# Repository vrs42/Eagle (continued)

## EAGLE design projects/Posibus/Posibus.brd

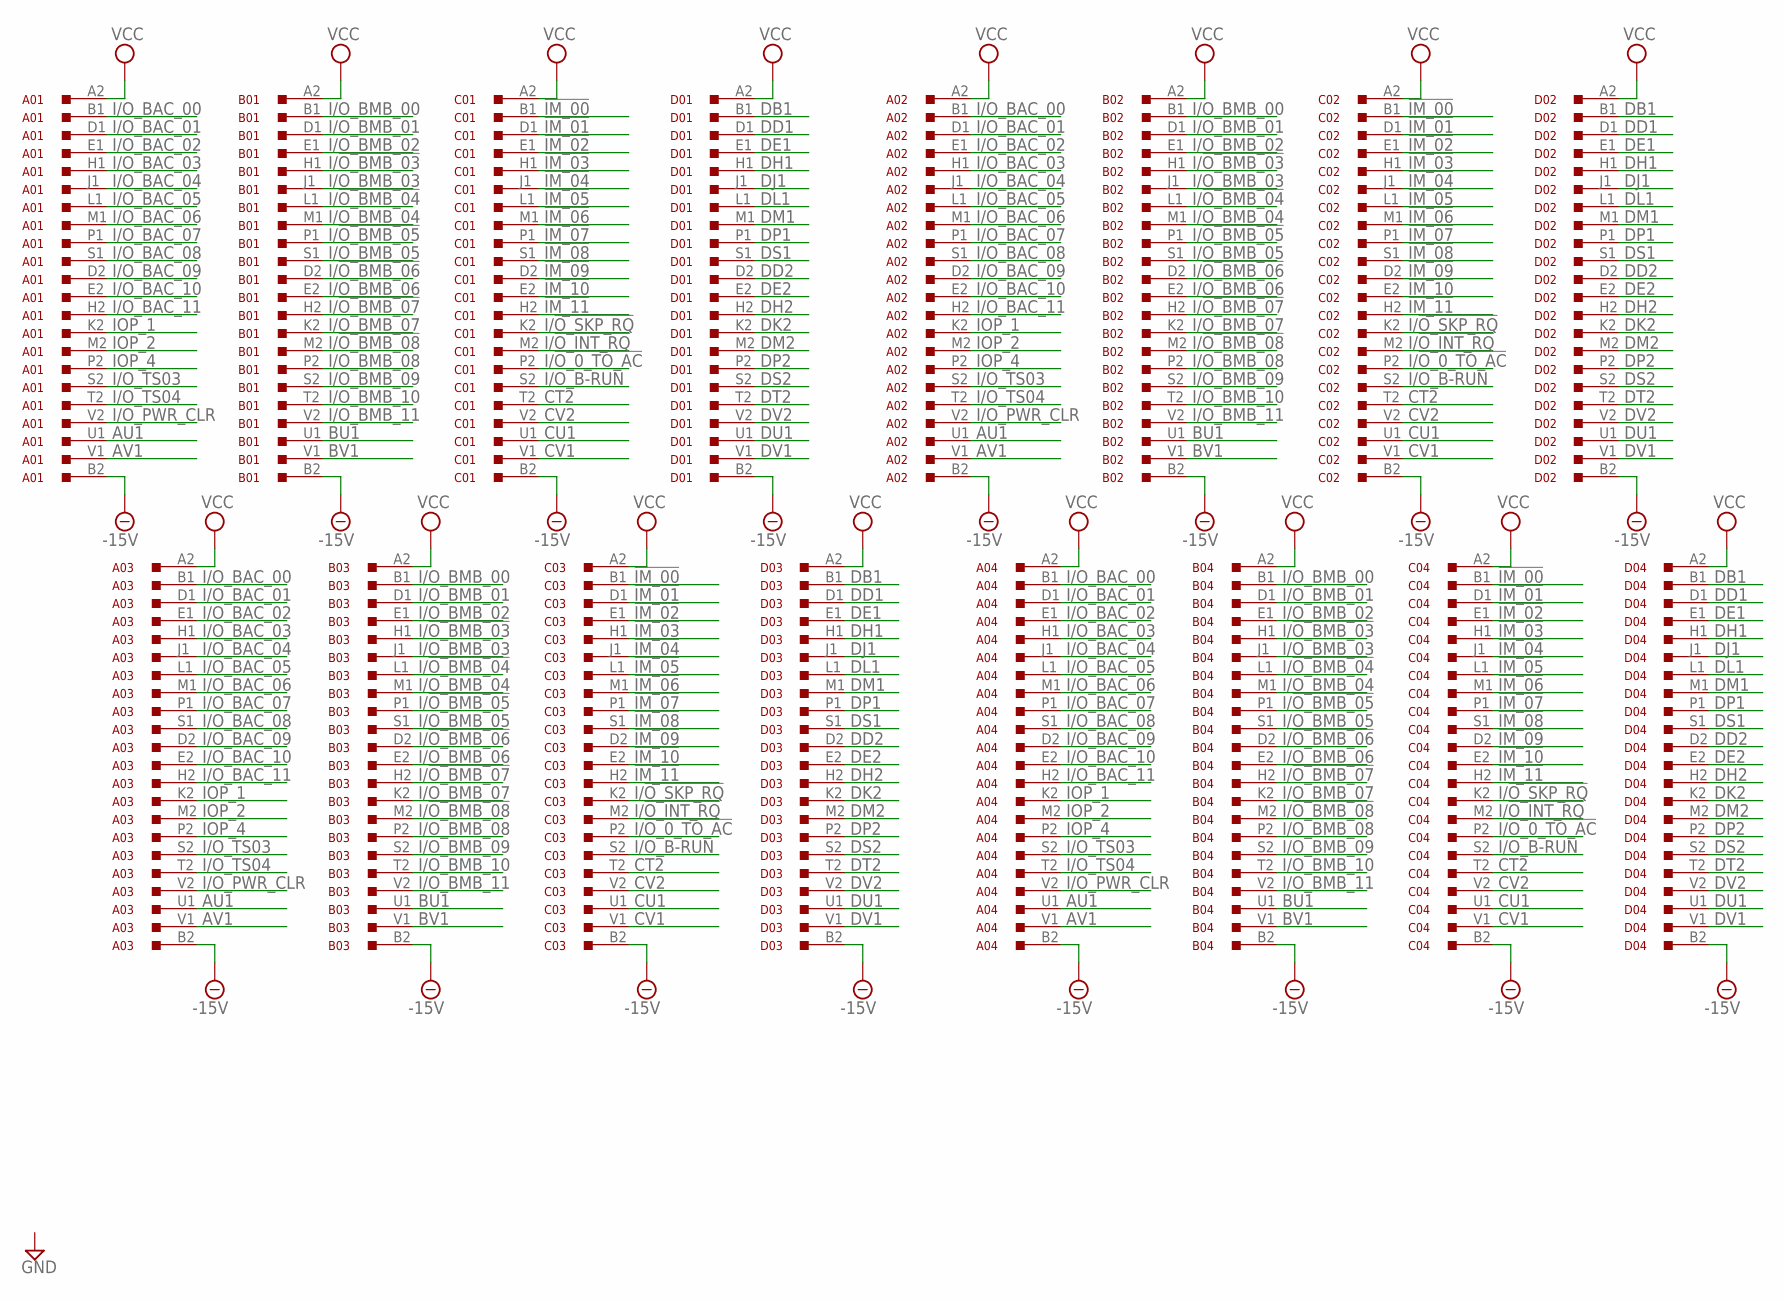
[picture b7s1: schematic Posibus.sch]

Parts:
A01, A02, A03, A04: M903; H807
B01, B02, B03, B04: M903; H807
C01, C02, C03, C04: M903; H807
D01, D02, D03, D04: M903; H807

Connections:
!IM_00: C01.B1, C02.B1, C03.B1, C04.B1
!IM_01: C01.D1, C02.D1, C03.D1, C04.D1
!IM_02: C01.E1, C02.E1, C03.E1, C04.E1
!IM_03: C01.H1, C02.H1, C03.H1, C04.H1
!IM_04: C01.J1, C02.J1, C03.J1, C04.J1
!IM_05: C01.L1, C02.L1, C03.L1, C04.L1
!IM_06: C01.M1, C02.M1, C03.M1, C04.M1
!IM_07: C01.P1, C02.P1, C03.P1, C04.P1
!IM_08: C01.S1, C02.S1, C03.S1, C04.S1
!IM_09: C01.D2, C02.D2, C03.D2, C04.D2
!IM_10: C01.E2, C02.E2, C03.E2, C04.E2
!IM_11: C01.H2, C02.H2, C03.H2, C04.H2
-15V: A01.B2, A02.B2, A03.B2, A04.B2, B01.B2, B02.B2, B03.B2, B04.B2, C01.B2, C02.B2, C03.B2, C04.B2, D01.B2, D02.B2, D03.B2, D04.B2
AU1: A01.U1, A02.U1, A03.U1, A04.U1
AV1: A01.V1, A02.V1, A03.V1, A04.V1
BU1: B01.U1, B02.U1, B03.U1, B04.U1
BV1: B01.V1, B02.V1, B03.V1, B04.V1
CT2: C01.T2, C02.T2, C03.T2, C04.T2
CU1: C01.U1, C02.U1, C03.U1, C04.U1
CV1: C01.V1, C02.V1, C03.V1, C04.V1
CV2: C01.V2, C02.V2, C03.V2, C04.V2
DB1: D01.B1, D02.B1, D03.B1, D04.B1
DD1: D01.D1, D02.D1, D03.D1, D04.D1
DD2: D01.D2, D02.D2, D03.D2, D04.D2
DE1: D01.E1, D02.E1, D03.E1, D04.E1
DE2: D01.E2, D02.E2, D03.E2, D04.E2
DH1: D01.H1, D02.H1, D03.H1, D04.H1
DH2: D01.H2, D02.H2, D03.H2, D04.H2
DJ1: D01.J1, D02.J1, D03.J1, D04.J1
DK2: D01.K2, D02.K2, D03.K2, D04.K2
DL1: D01.L1, D02.L1, D03.L1, D04.L1
DM1: D01.M1, D02.M1, D03.M1, D04.M1
DM2: D01.M2, D02.M2, D03.M2, D04.M2
DP1: D01.P1, D02.P1, D03.P1, D04.P1
DP2: D01.P2, D02.P2, D03.P2, D04.P2
DS1: D01.S1, D02.S1, D03.S1, D04.S1
DS2: D01.S2, D02.S2, D03.S2, D04.S2
DT2: D01.T2, D02.T2, D03.T2, D04.T2
DU1: D01.U1, D02.U1, D03.U1, D04.U1
DV1: D01.V1, D02.V1, D03.V1, D04.V1
DV2: D01.V2, D02.V2, D03.V2, D04.V2
GND: A01.A1 (GND), A01.C1 (GND), A01.C2 (GND), A01.F1 (GND), A01.F2 (GND), A01.J2 (GND), A01.K1 (GND), A01.L2 (GND), A01.N1 (GND), A01.N2 (GND), A01.R1 (GND), A01.R2 (GND), A01.T1 (GND), A01.U2 (GND), A02.A1 (GND), A02.C1 (GND), A02.C2 (GND), A02.F1 (GND), A02.F2 (GND), A02.J2 (GND), A02.K1 (GND), A02.L2 (GND), A02.N1 (GND), A02.N2 (GND), A02.R1 (GND), A02.R2 (GND), A02.T1 (GND), A02.U2 (GND), A03.A1 (GND), A03.C1 (GND), A03.C2 (GND), A03.F1 (GND), A03.F2 (GND), A03.J2 (GND), A03.K1 (GND), A03.L2 (GND), A03.N1 (GND), A03.N2 (GND), A03.R1 (GND), A03.R2 (GND), A03.T1 (GND), A03.U2 (GND), A04.A1 (GND), A04.C1 (GND), A04.C2 (GND), A04.F1 (GND), A04.F2 (GND), A04.J2 (GND), A04.K1 (GND), A04.L2 (GND), A04.N1 (GND), A04.N2 (GND), A04.R1 (GND), A04.R2 (GND), A04.T1 (GND), A04.U2 (GND), B01.A1 (GND), B01.C1 (GND), B01.C2 (GND), B01.F1 (GND), B01.F2 (GND), B01.J2 (GND), B01.K1 (GND), B01.L2 (GND), B01.N1 (GND), B01.N2 (GND), B01.R1 (GND), B01.R2 (GND), B01.T1 (GND), B01.U2 (GND), B02.A1 (GND), B02.C1 (GND), B02.C2 (GND), B02.F1 (GND), B02.F2 (GND), B02.J2 (GND), B02.K1 (GND), B02.L2 (GND), B02.N1 (GND), B02.N2 (GND), B02.R1 (GND), B02.R2 (GND), B02.T1 (GND), B02.U2 (GND), B03.A1 (GND), B03.C1 (GND), B03.C2 (GND), B03.F1 (GND), B03.F2 (GND), B03.J2 (GND), B03.K1 (GND), B03.L2 (GND), B03.N1 (GND), B03.N2 (GND), B03.R1 (GND), B03.R2 (GND), B03.T1 (GND), B03.U2 (GND), B04.A1 (GND), B04.C1 (GND), B04.C2 (GND), B04.F1 (GND), B04.F2 (GND), B04.J2 (GND), B04.K1 (GND), B04.L2 (GND), B04.N1 (GND), B04.N2 (GND), B04.R1 (GND), B04.R2 (GND), B04.T1 (GND), B04.U2 (GND), C01.A1 (GND), C01.C1 (GND), C01.C2 (GND), C01.F1 (GND), C01.F2 (GND), C01.J2 (GND), C01.K1 (GND), C01.L2 (GND), C01.N1 (GND), C01.N2 (GND), C01.R1 (GND), C01.R2 (GND), C01.T1 (GND), C01.U2 (GND), C02.A1 (GND), C02.C1 (GND), C02.C2 (GND), C02.F1 (GND), C02.F2 (GND), C02.J2 (GND), C02.K1 (GND), C02.L2 (GND), C02.N1 (GND), C02.N2 (GND), C02.R1 (GND), C02.R2 (GND), C02.T1 (GND), C02.U2 (GND), C03.A1 (GND), C03.C1 (GND), C03.C2 (GND), C03.F1 (GND), C03.F2 (GND), C03.J2 (GND), C03.K1 (GND), C03.L2 (GND), C03.N1 (GND), C03.N2 (GND), C03.R1 (GND), C03.R2 (GND), C03.T1 (GND), C03.U2 (GND), C04.A1 (GND), C04.C1 (GND), C04.C2 (GND), C04.F1 (GND), C04.F2 (GND), C04.J2 (GND), C04.K1 (GND), C04.L2 (GND), C04.N1 (GND), C04.N2 (GND), C04.R1 (GND), C04.R2 (GND), C04.T1 (GND), C04.U2 (GND), D01.A1 (GND), D01.C1 (GND), D01.C2 (GND), D01.F1 (GND), D01.F2 (GND), D01.J2 (GND), D01.K1 (GND), D01.L2 (GND), D01.N1 (GND), D01.N2 (GND), D01.R1 (GND), D01.R2 (GND), D01.T1 (GND), D01.U2 (GND), D02.A1 (GND), D02.C1 (GND), D02.C2 (GND), D02.F1 (GND), D02.F2 (GND), D02.J2 (GND), D02.K1 (GND), D02.L2 (GND), D02.N1 (GND), D02.N2 (GND), D02.R1 (GND), D02.R2 (GND), D02.T1 (GND), D02.U2 (GND), D03.A1 (GND), D03.C1 (GND), D03.C2 (GND), D03.F1 (GND), D03.F2 (GND), D03.J2 (GND), D03.K1 (GND), D03.L2 (GND), D03.N1 (GND), D03.N2 (GND), D03.R1 (GND), D03.R2 (GND), D03.T1 (GND), D03.U2 (GND), D04.A1 (GND), D04.C1 (GND), D04.C2 (GND), D04.F1 (GND), D04.F2 (GND), D04.J2 (GND), D04.K1 (GND), D04.L2 (GND), D04.N1 (GND), D04.N2 (GND), D04.R1 (GND), D04.R2 (GND), D04.T1 (GND), D04.U2 (GND)
I/!O_0_TO_AC: C01.P2, C02.P2, C03.P2, C04.P2
I/!O_BMB_03: B01.H1, B02.H1, B03.H1, B04.H1
I/!O_BMB_04: B01.L1, B02.L1, B03.L1, B04.L1
I/!O_BMB_05: B01.P1, B02.P1, B03.P1, B04.P1
I/!O_BMB_06: B01.D2, B02.D2, B03.D2, B04.D2
I/!O_BMB_07: B01.H2, B02.H2, B03.H2, B04.H2
I/!O_BMB_08: B01.M2, B02.M2, B03.M2, B04.M2
I/!O_INT_RQ: C01.M2, C02.M2, C03.M2, C04.M2
I/!O_SKP_RQ: C01.K2, C02.K2, C03.K2, C04.K2
I/O_B-RUN: C01.S2, C02.S2, C03.S2, C04.S2
I/O_BAC_00: A01.B1, A02.B1, A03.B1, A04.B1
I/O_BAC_01: A01.D1, A02.D1, A03.D1, A04.D1
I/O_BAC_02: A01.E1, A02.E1, A03.E1, A04.E1
I/O_BAC_03: A01.H1, A02.H1, A03.H1, A04.H1
I/O_BAC_04: A01.J1, A02.J1, A03.J1, A04.J1
I/O_BAC_05: A01.L1, A02.L1, A03.L1, A04.L1
I/O_BAC_06: A01.M1, A02.M1, A03.M1, A04.M1
I/O_BAC_07: A01.P1, A02.P1, A03.P1, A04.P1
I/O_BAC_08: A01.S1, A02.S1, A03.S1, A04.S1
I/O_BAC_09: A01.D2, A02.D2, A03.D2, A04.D2
I/O_BAC_10: A01.E2, A02.E2, A03.E2, A04.E2
I/O_BAC_11: A01.H2, A02.H2, A03.H2, A04.H2
I/O_BMB_00: B01.B1, B02.B1, B03.B1, B04.B1
I/O_BMB_01: B01.D1, B02.D1, B03.D1, B04.D1
I/O_BMB_02: B01.E1, B02.E1, B03.E1, B04.E1
I/O_BMB_03: B01.J1, B02.J1, B03.J1, B04.J1
I/O_BMB_04: B01.M1, B02.M1, B03.M1, B04.M1
I/O_BMB_05: B01.S1, B02.S1, B03.S1, B04.S1
I/O_BMB_06: B01.E2, B02.E2, B03.E2, B04.E2
I/O_BMB_07: B01.K2, B02.K2, B03.K2, B04.K2
I/O_BMB_08: B01.P2, B02.P2, B03.P2, B04.P2
I/O_BMB_09: B01.S2, B02.S2, B03.S2, B04.S2
I/O_BMB_10: B01.T2, B02.T2, B03.T2, B04.T2
I/O_BMB_11: B01.V2, B02.V2, B03.V2, B04.V2
I/O_PWR_CLR: A01.V2, A02.V2, A03.V2, A04.V2
I/O_TS03: A01.S2, A02.S2, A03.S2, A04.S2
I/O_TS04: A01.T2, A02.T2, A03.T2, A04.T2
IOP_1: A01.K2, A02.K2, A03.K2, A04.K2
IOP_2: A01.M2, A02.M2, A03.M2, A04.M2
IOP_4: A01.P2, A02.P2, A03.P2, A04.P2
VCC: A01.A2, A02.A2, A03.A2, A04.A2, B01.A2, B02.A2, B03.A2, B04.A2, C01.A2, C02.A2, C03.A2, C04.A2, D01.A2, D02.A2, D03.A2, D04.A2

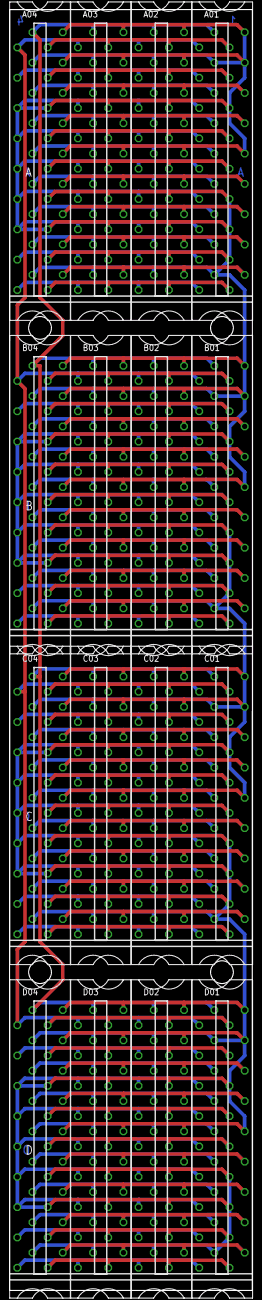
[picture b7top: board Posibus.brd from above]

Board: 2 copper layers, 50.9 x 268.3 mm, 16 parts (0 on the bottom side), 83 nets.
